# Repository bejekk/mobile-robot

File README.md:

# Robot mobilny — praca inżynierska

Konstrukcja i oprogramowanie czterokołowego (gąsienicowego) robota mobilnego.
Firmware czasu rzeczywistego na **STM32H755**, sterowanie z **ROS 2 Humble** na Jetson Nano, płyta główna w **KiCad** oraz modele mechaniczne przekładni i obudowy.

Autor: **Błażej Kruszka**, Uniwersytet Mikołaja Kopernika w Toruniu, 2025–2026.

## Architektura

```
gamepad  →  ROS 2 (Jetson)  →  UART 115200  →  STM32H755
                 │                                  │
                 └── /telemetry ← prędkości PI ← enkodery DC, PWM, A4988
```

- **STM32 (CM7)** — enkodery, regulatory PI, mostki H (4× DC), silniki krokowe (4× A4988), protokół UART.
- **ROS 2** — odczyt pada, mostek szeregowy, logger telemetrii.
- **PCB** — płyta główna pod Nucleo-H755, 8 kanałów wykonawczych i interfejsy czujników.

## Struktura repozytorium

| Katalog | Zawartość |
| --- | --- |
| `firmware/` | Projekt STM32CubeIDE (dual-core STM32H755ZITX), bez artefaktów kompilacji |
| `ros2_ws/` | Pakiet `robot_control` + Dockerfile |
| `pcb/` | KiCad (schemat, PCB, Gerber) |
| `mechanical/` | Modele STL i archiwum Fusion 360 |
| `control/` | Skrypt MATLAB do identyfikacji regulatorów PI |
| `docs/` | Praca, prezentacja, opis protokołu UART |

Nie ma tu notatek roboczych, dumpów CubeIDE, kopii zapasowych KiCad, filmów ani cudzych prac.

## Firmware (STM32)

Otwórz folder `firmware/` w STM32CubeIDE (projekt dual-core nadal nazywa się `jakie_wyjscia` — tak zapisał CubeMX). Zbuduj konfigurację **CM7 Debug** oraz CM4, jeśli boot dual-core ma zostać zachowany.

Aplikacja użytkownika:

- `firmware/CM7/Core/Src/PI.c` — pomiar prędkości z enkodera, filtr i regulator PI z rampą oraz anti-windup
- `firmware/CM7/Core/Src/motor_control.c` — PWM + kierunek mostka H, sleep/dir silników krokowych
- `firmware/CM7/Core/Src/main.c` — parser UART, pętla 10 ms, telemetria

Po resecie STM32 czeka na komendę `ready` (buzzer), dopiero potem przyjmuje zadawanie prędkości i krokowych.

## ROS 2

Wymagania: ROS 2 Humble, `python3-serial`, pakiet `inputs`.

```bash
cd ros2_ws
source /opt/ros/humble/setup.bash
colcon build --symlink-install
source install/setup.bash
ros2 launch robot_control robot.launch.py
```

Port UART można zmienić parametrem węzła `stm_bridge`:

```bash
ros2 run robot_control stm_bridge --ros-args -p port:=/dev/ttyACM0 -p baudrate:=115200
```

### Docker (Jetson)

```bash
cd ros2_ws
sudo docker build -t robot_control:humble .
xhost +local:root
sudo docker run -it --rm --network host \
  --runtime nvidia \
  -e DISPLAY=$DISPLAY \
  -v /tmp/.X11-unix:/tmp/.X11-unix \
  --device /dev/input/js0 \
  --device /dev/ttyACM0 \
  robot_control:humble
```

W kontenerze: `source /home/ros_user/ws/install/setup.bash && ros2 launch robot_control robot.launch.py`.

## MATLAB

`control/pi_identification.m` wysyła sekwencję skoków `lspeed`/`rspeed` i rysuje zadanie vs. pomiar dla czterech kół. Ustaw `portName` na swój port (`COM18` w Windows, `/dev/ttyACM0` w Linux).

## PCB

Projekt KiCad 8: `pcb/PCBV2.kicad_pro`. Gerbery do produkcji są w `pcb/gerber/`. Podgląd schematu: `pcb/PCBV2.pdf`.

## Protokół UART

Zobacz [docs/uart.md](docs/uart.md).

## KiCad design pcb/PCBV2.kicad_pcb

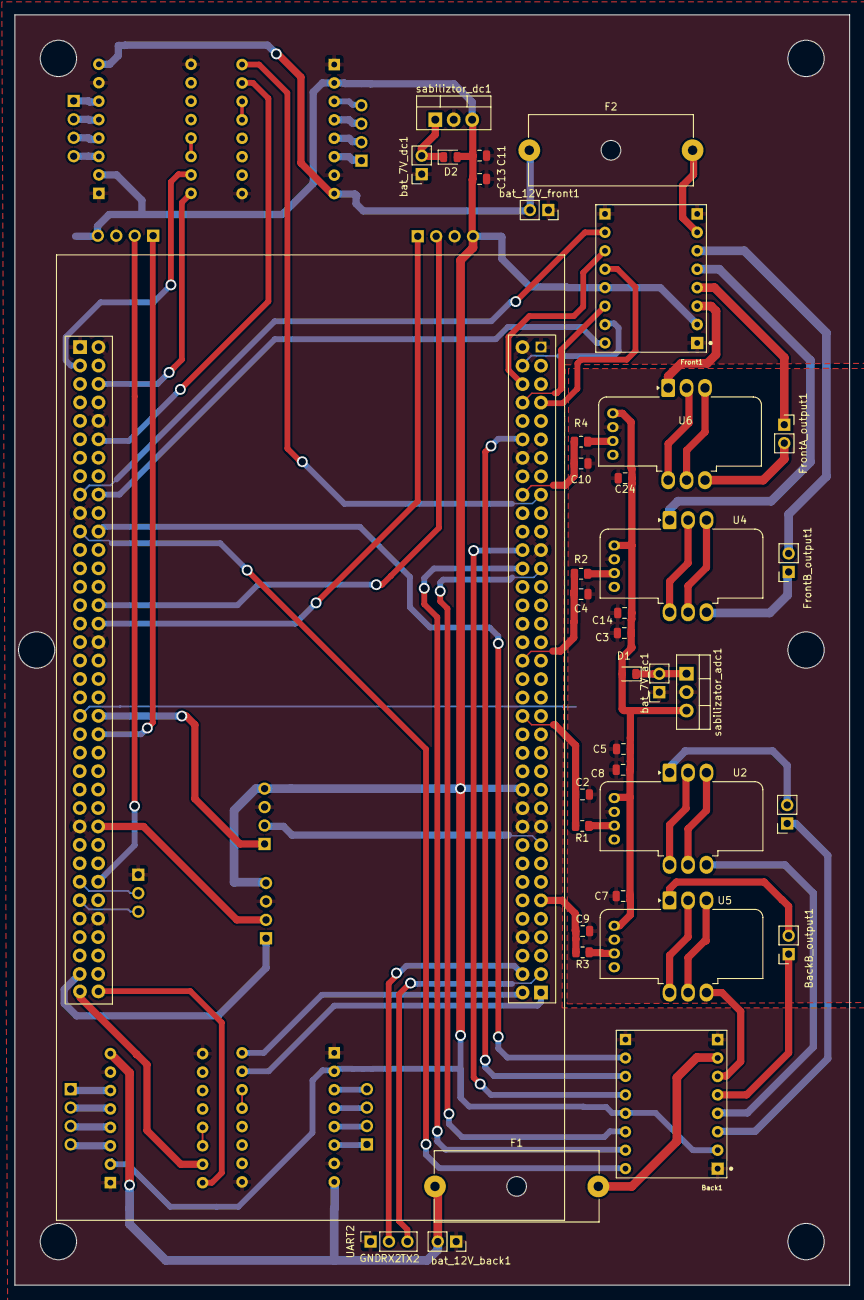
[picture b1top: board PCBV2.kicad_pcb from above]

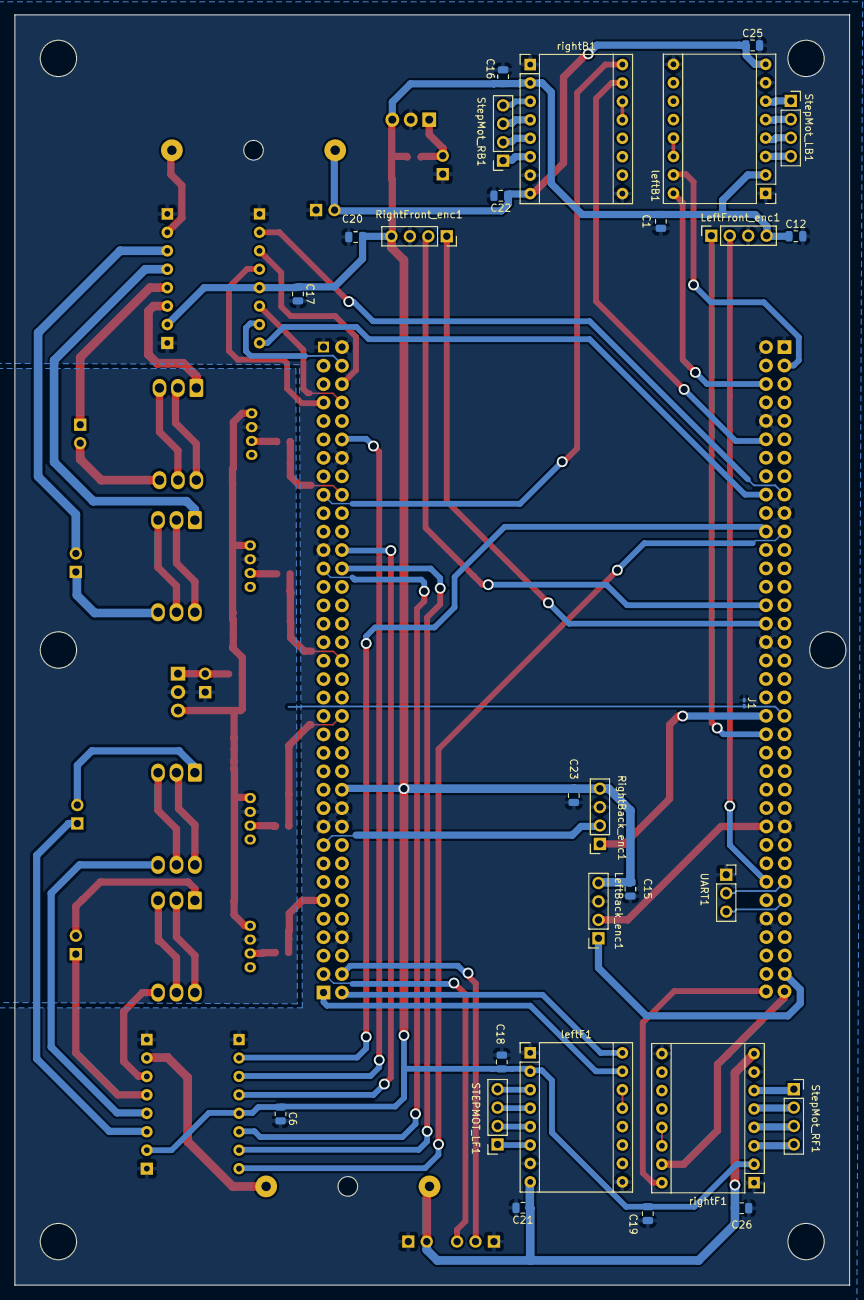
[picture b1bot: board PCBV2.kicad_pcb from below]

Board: 4 copper layers, 115.0 x 175.0 mm, 66 parts (28 on the bottom side), 89 nets.

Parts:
Back1: TB6612FNG; SHIELD_POLOLU-713
BackB_output1: PinSocket_1x02_P2.54mm_Vertical
BazkB_output1: PinSocket_1x02_P2.54mm_Vertical
C1, C2, C3, C4, C6, C7, C8, C9, C10, C11, C12, C14, C15, C16, C17, C18, C19, C20, C21, C22, C23, C24, C25, C26: 100nF; C_0805_2012Metric
C5, C13: 100uF; C_0805_2012Metric
D1, D2: D_Filled; D_0805_2012Metric
F1, F2: Fuse; Fuseholder_Cylinder-5x20mm_Schurter_0031_8201_Horizontal_Op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
Front1: TB6612FNG; SHIELD_POLOLU-713
FrontA_output1: PinSocket_1x02_P2.54mm_Vertical
FrontB_output1: PinSocket_1x02_P2.54mm_Vertical
J1: zworaGND; R_0201_0603Metric_Pad0.64x0.40mm_HandSolder
LeftBack_enc1: Conn_01x04_Pin; PinSocket_1x04_P2.54mm_Vertical
LeftFront_enc1: Conn_01x04_Pin; PinSocket_1x04_P2.54mm_Vertical
R1, R2, R3, R4: 3.2K; R_0805_2012Metric
RightBack_enc1: Conn_01x04_Pin; PinSocket_1x04_P2.54mm_Vertical
RightFront_enc1: Conn_01x04_Pin; PinSocket_1x04_P2.54mm_Vertical
STEPMOT_LF1: Conn_01x04_Pin; PinSocket_1x04_P2.54mm_Vertical
StepMot_LB1: Conn_01x04_Pin; PinSocket_1x04_P2.54mm_Vertical
StepMot_RB1: Conn_01x04_Pin; PinSocket_1x04_P2.54mm_Vertical
StepMot_RF1: Conn_01x04_Pin; PinSocket_1x04_P2.54mm_Vertical
U1: STM32H755
U2, U4, U5, U6: LTSR6-NP; LEM_LTSR-NP
UART1: UART1; PinSocket_1x03_P2.54mm_Vertical
UART2: UART2; PinSocket_1x03_P2.54mm_Vertical
bat_7V_ac1, bat_7V_dc1, bat_12V_back1, bat_12V_front1: PinSocket_1x02_P2.54mm_Vertical
leftB1: Pololu_Breakout_A4988; Pololu_Breakout-16_15.2x20.3mm
leftF1: Pololu_Breakout_A4988; Pololu_Breakout-16_15.2x20.3mm
rightB1: Pololu_Breakout_A4988; Pololu_Breakout-16_15.2x20.3mm
rightF1: Pololu_Breakout_A4988; Pololu_Breakout-16_15.2x20.3mm
sabilizator_adc1: LM2940T-5.0_NOPB; TO-220-3_Vertical
sabiliztor_dc1: LM2940T-5.0_NOPB; TO-220-3_Vertical

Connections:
7V: D1.1 (K), D2.1 (K), bat_7V_ac1.2, bat_7V_dc1.2, sabilizator_adc1.1 (IN), sabiliztor_dc1.1 (IN)
12V: C21.1, C22.1, C25.1, C26.1, F1.1, F2.1, bat_12V_back1.2, bat_12V_front1.2, leftB1.8 (VMOT), leftF1.8 (VMOT), rightB1.8 (VMOT), rightF1.8 (VMOT)
+5V: Back1.2 (VCC), Back1.13 (STBY), C1.1, C6.1, C11.2, C12.1, C13.1, C15.1, C16.1, C17.1, C18.1, C19.1, C20.1, C23.1, D2.2 (A), Front1.2 (VCC), Front1.13 (STBY), LeftBack_enc1.4, LeftFront_enc1.4, RightBack_enc1.4, RightFront_enc1.4, U1.VIN, leftB1.2 (VDD), leftF1.2 (VDD), rightB1.2 (VDD), rightF1.2 (VDD), sabiliztor_dc1.3 (OUT)
+5VA: C3.2, C5.1, C7.1, C8.1, C14.1, C24.1, D1.2 (A), U2.10 (+5V), U4.10 (+5V), U5.10 (+5V), U6.10 (+5V), sabilizator_adc1.3 (OUT)
/ADC1: C2.1, R1.2, U1.PA4
/ADC2: C4.2, R2.2, U1.PC0
/ADC3: C9.1, R3.2, U1.PF7
/ADC4: C10.2, R4.2, U1.PF9
/AIN1_Back: Back1.14 (AIN1), U1.PE3
/AIN1_Front: Front1.14 (AIN1), U1.PG10
/AIN2_Back: Back1.15 (AIN2), U1.PE4
/AIN2_Front: Front1.15 (AIN2), U1.PG11
/BIN1_Back: Back1.12 (BIN1), U1.PE5
/BIN1_Front: Front1.12 (BIN1), U1.PG12
/BIN2_Back: Back1.11 (BIN2), U1.PE6
/BIN2_Front: Front1.11 (BIN2), U1.PG13
/DIR_LB: U1.PG7, leftB1.16 (DIR)
/DIR_LF: U1.PC11, leftF1.16 (DIR)
/DIR_RB: U1.PD1, rightB1.16 (DIR)
/DIR_RF: U1.PC9, rightF1.16 (DIR)
/LB_encA: LeftBack_enc1.1, U1.PC6
/LB_encB: LeftBack_enc1.2, U1.PC7
/LF_encA: LeftFront_enc1.2, U1.PA6
/LF_encB: LeftFront_enc1.1, U1.PB5
/PWMA_B: Back1.16 (PWMA), U1.PE9
/PWMA_F: Front1.16 (PWMA), U1.PE13
/PWMB_B: Back1.10 (PWMB), U1.PE14
/PWMB_F: Front1.10 (PWMB), U1.PE11
/RB_encA: RightBack_enc1.2, U1.PA15
/RB_encB: RightBack_enc1.1, U1.PB3
/RF_encA: RightFront_enc1.2, U1.PD12
/RF_encB: RightFront_enc1.1, U1.PD13
/RX1: U1.PA11, UART1.2
/RX2: U1.PD2, UART2.2
/STEP_LB: U1.PG6, leftB1.15 (STEP)
/STEP_LF: U1.PC10, leftF1.15 (STEP)
/STEP_RB: U1.PG14, rightB1.15 (STEP)
/STEP_RF: U1.PC8, rightF1.15 (STEP)
/SensBAIN: Back1.4 (AO2), U2.4 (OUT4)
/SensBAOut: BazkB_output1.2, U2.1 (IN1)
/SensBBIN: Back1.6 (BO1), U5.4 (OUT4)
/SensBBOut: BackB_output1.2, U5.1 (IN1)
/SensFAIN: Front1.3 (AO1), U6.1 (IN1)
/SensFAOut: FrontA_output1.2, U6.4 (OUT4)
/SensFBIN: Front1.5 (BO2), U4.1 (IN1)
/SensFBOut: FrontB_output1.1, U4.4 (OUT4)
/TX1: U1.PA12, UART1.3
/TX2: U1.PC12, UART2.3
GND: Back1.1 (GND), Back1.8 (PGND1), Back1.9 (PGND2), C1.2, C6.2, C11.1, C12.2, C13.2, C15.2, C16.2, C17.2, C18.2, C19.2, C20.2, C21.2, C22.2, C23.2, C25.2, C26.2, Front1.1 (GND), Front1.8 (PGND1), Front1.9 (PGND2), J1.1, LeftBack_enc1.3, LeftFront_enc1.3, RightBack_enc1.3, RightFront_enc1.3, U1.GND, UART1.1, UART2.1, bat_7V_dc1.1, bat_12V_back1.1, bat_12V_front1.1, leftB1.1 (GND), leftB1.7 (GND), leftB1.9 (~ENABLE), leftF1.1 (GND), leftF1.7 (GND), leftF1.9 (~ENABLE), rightB1.1 (GND), rightB1.7 (GND), rightB1.9 (~ENABLE), rightF1.1 (GND), rightF1.7 (GND), rightF1.9 (~ENABLE), sabiliztor_dc1.2 (GND)
GNDA: C2.2, C3.1, C4.1, C5.2, C7.2, C8.2, C9.2, C10.1, C14.2, C24.2, U2.9 (0V), U4.9 (0V), U5.9 (0V), U6.9 (0V), bat_7V_ac1.1, sabilizator_adc1.2 (GND)
unnamed: Back1.3 (AO1), BazkB_output1.1
unnamed: Back1.5 (BO2), BackB_output1.1
unnamed: Back1.7 (VMOT), F1.2
unnamed: Front1.4 (AO2), FrontA_output1.1
unnamed: Front1.6 (BO1), FrontB_output1.2
unnamed: F2.2, Front1.7 (VMOT)
unnamed: J1.2, U1.AGND
unnamed: STEPMOT_LF1.1, leftF1.6 (2B)
unnamed: STEPMOT_LF1.2, leftF1.5 (2A)
unnamed: STEPMOT_LF1.3, leftF1.4 (1A)
unnamed: STEPMOT_LF1.4, leftF1.3 (1B)
unnamed: StepMot_LB1.1, leftB1.6 (2B)
unnamed: StepMot_LB1.2, leftB1.5 (2A)
unnamed: StepMot_LB1.3, leftB1.4 (1A)
unnamed: StepMot_LB1.4, leftB1.3 (1B)
unnamed: StepMot_RB1.1, rightB1.6 (2B)
unnamed: StepMot_RB1.2, rightB1.5 (2A)
unnamed: StepMot_RB1.3, rightB1.4 (1A)
unnamed: StepMot_RB1.4, rightB1.3 (1B)
unnamed: StepMot_RF1.1, rightF1.6 (2B)
unnamed: StepMot_RF1.2, rightF1.5 (2A)
unnamed: StepMot_RF1.3, rightF1.4 (1A)
unnamed: StepMot_RF1.4, rightF1.3 (1B)
unnamed: U2.2 (IN2), U2.6 (OUT6)
unnamed: U2.3 (IN3), U2.5 (OUT5)
unnamed: R1.1, U2.8 (Out)
unnamed: U4.2 (IN2), U4.6 (OUT6)
unnamed: U4.3 (IN3), U4.5 (OUT5)
unnamed: R2.1, U4.8 (Out)
unnamed: U5.2 (IN2), U5.6 (OUT6)
unnamed: U5.3 (IN3), U5.5 (OUT5)
unnamed: R3.1, U5.8 (Out)
unnamed: U6.2 (IN2), U6.6 (OUT6)
unnamed: U6.3 (IN3), U6.5 (OUT5)
unnamed: R4.1, U6.8 (Out)
unnamed: leftB1.13 (~RESET), leftB1.14 (~SLEEP)
unnamed: leftF1.13 (~RESET), leftF1.14 (~SLEEP)
unnamed: rightB1.13 (~RESET), rightB1.14 (~SLEEP)
unnamed: rightF1.13 (~RESET), rightF1.14 (~SLEEP)

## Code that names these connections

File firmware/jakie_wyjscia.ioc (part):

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Mcu.Name=STM32H755ZITx
Mcu.Package=LQFP144
Mcu.UserName=STM32H755ZITx
PA0.GPIOParameters=PinAttribute
PA0.Mode=MII
PA0.PinAttribute=CortexM7
PA0.Signal=ETH_CRS
PA1.GPIOParameters=PinAttribute
PA1.Mode=MII
PA1.PinAttribute=CortexM7
PA1.Signal=ETH_RX_CLK
PA11.GPIOParameters=PinAttribute
PA11.Mode=Asynchronous
PA11.PinAttribute=CortexM7
PA11.Signal=UART4_RX
PA12.GPIOParameters=PinAttribute
PA12.Mode=Asynchronous
PA12.PinAttribute=CortexM7
PA12.Signal=UART4_TX
PA15\ (JTDI).GPIOParameters=PinAttribute
PA15\ (JTDI).PinAttribute=CortexM7
PA15\ (JTDI).Signal=S_TIM2_CH1_ETR
PA2.GPIOParameters=PinAttribute
PA2.Mode=MII
PA2.PinAttribute=CortexM7
PA2.Signal=ETH_MDIO
PA3.GPIOParameters=PinAttribute
PA3.Mode=MII
PA3.PinAttribute=CortexM7
PA3.Signal=ETH_COL
PA5.GPIOParameters=PinAttribute
PA5.Mode=Full_Duplex_Master
PA5.PinAttribute=CortexM7
PA5.Signal=SPI1_SCK
PA6.GPIOParameters=PinAttribute
PA6.PinAttribute=CortexM7
PA6.Signal=S_TIM3_CH1
PA7.GPIOParameters=PinAttribute
PA7.Mode=MII
PA7.PinAttribute=CortexM7
PA7.Signal=ETH_RX_DV
PB0.GPIOParameters=PinAttribute
PB0.Mode=MII
PB0.PinAttribute=CortexM7
PB0.Signal=ETH_RXD2
PB1.GPIOParameters=PinAttribute
PB1.Mode=MII
PB1.PinAttribute=CortexM7
PB1.Signal=ETH_RXD3
PB11.GPIOParameters=PinAttribute
PB11.Mode=MII
PB11.PinAttribute=CortexM7
PB11.Signal=ETH_TX_EN
PB12.GPIOParameters=PinAttribute
PB12.Mode=MII
PB12.PinAttribute=CortexM7
PB12.Signal=ETH_TXD0
PB13.GPIOParameters=PinAttribute
PB13.Mode=MII
PB13.PinAttribute=CortexM7
PB13.Signal=ETH_TXD1
PB3\ (JTDO/TRACESWO).GPIOParameters=PinAttribute
PB3\ (JTDO/TRACESWO).PinAttribute=CortexM7
PB3\ (JTDO/TRACESWO).Signal=S_TIM2_CH2
PB5.GPIOParameters=PinAttribute
PB5.PinAttribute=CortexM7
PB5.Signal=S_TIM3_CH2
PB6.GPIOParameters=PinAttribute
PB6.Mode=I2C
PB6.PinAttribute=CortexM7
PB6.Signal=I2C1_SCL
PB7.GPIOParameters=PinAttribute
PB7.Mode=I2C
PB7.PinAttribute=CortexM7
PB7.Signal=I2C1_SDA
PB8.ContextOwner=CortexM7
PB8.GPIOParameters=GPIO_Label,GPIO_FM8,PinAttribute
PB8.GPIO_FM8=__NULL
PB8.GPIO_Label=SLEEP_RF
PB8.PinAttribute=CortexM7
PB8.Signal=GPIO_Output
PB9.ContextOwner=CortexM7
PB9.GPIOParameters=GPIO_Label,PinAttribute,GPIO_FM9
PB9.GPIO_FM9=__NULL
PB9.GPIO_Label=SLEEP_LF
PB9.PinAttribute=CortexM7
PB9.Signal=GPIO_Output
PC0.GPIOParameters=PinAttribute
PC0.PinAttribute=CortexM7
PC0.Signal=ADCx_INP10
PC1.GPIOParameters=PinAttribute
PC1.Mode=MII
PC1.PinAttribute=CortexM7
PC1.Signal=ETH_MDC
PC10.ContextOwner=CortexM7
PC10.GPIOParameters=GPIO_Label,PinAttribute
PC10.GPIO_Label=STEP_LF
PC10.PinAttribute=CortexM7
PC10.Signal=GPIO_Output
PC11.ContextOwner=CortexM7
PC11.GPIOParameters=GPIO_Label,PinAttribute
PC11.GPIO_Label=DIR_LF
PC11.PinAttribute=CortexM7
PC11.Signal=GPIO_Output
PC12.GPIOParameters=PinAttribute
PC12.Mode=Asynchronous
PC12.PinAttribute=CortexM7
PC12.Signal=UART5_TX
PC2_C.GPIOParameters=PinAttribute
PC2_C.Mode=MII
PC2_C.PinAttribute=CortexM7
PC2_C.Signal=ETH_TXD2
PC3_C.GPIOParameters=PinAttribute
PC3_C.Mode=MII
PC3_C.PinAttribute=CortexM7
PC3_C.Signal=ETH_TX_CLK
PC4.GPIOParameters=PinAttribute
PC4.Mode=MII
PC4.PinAttribute=CortexM7
PC4.Signal=ETH_RXD0
PC5.GPIOParameters=PinAttribute
PC5.Mode=MII
PC5.PinAttribute=CortexM7
PC5.Signal=ETH_RXD1
PC6.GPIOParameters=PinAttribute
PC6.PinAttribute=CortexM7
PC6.Signal=S_TIM8_CH1
PC7.GPIOParameters=PinAttribute
PC7.PinAttribute=CortexM7
PC7.Signal=S_TIM8_CH2
PC8.ContextOwner=CortexM7
PC8.GPIOParameters=GPIO_Label,PinAttribute
PC8.GPIO_Label=STEP_RF
PC8.PinAttribute=CortexM7
PC8.Signal=GPIO_Output
PC9.ContextOwner=CortexM7
PC9.GPIOParameters=GPIO_Label,PinAttribute
PC9.GPIO_Label=DIR_RF
PC9.PinAttribute=CortexM7
PC9.Signal=GPIO_Output
PD1.ContextOwner=CortexM7
PD1.GPIOParameters=GPIO_Label,PinAttribute
PD1.GPIO_Label=DIR_RB
PD1.PinAttribute=CortexM7
PD1.Signal=GPIO_Output
PD10.ContextOwner=CortexM7
PD10.GPIOParameters=GPIO_Label,PinAttribute
PD10.GPIO_Label=SLEEP_RB
PD10.PinAttribute=CortexM7
PD10.Signal=GPIO_Output
PD12.GPIOParameters=PinAttribute
PD12.PinAttribute=CortexM7
PD12.Signal=S_TIM4_CH1
PD13.GPIOParameters=PinAttribute
PD13.PinAttribute=CortexM7
PD13.Signal=S_TIM4_CH2
PD2.GPIOParameters=PinAttribute
PD2.Mode=Asynchronous
PD2.PinAttribute=CortexM7
PD2.Signal=UART5_RX
PD6.ContextOwner=CortexM7
PD6.GPIOParameters=PinAttribute
PD6.PinAttribute=CortexM7
PD6.Signal=GPIO_Output
PD7.GPIOParameters=PinAttribute
PD7.Mode=Full_Duplex_Master
PD7.PinAttribute=CortexM7
PD7.Signal=SPI1_MOSI
PD8.GPIOParameters=PinAttribute
PD8.Mode=Asynchronous
PD8.PinAttribute=CortexM7
PD8.Signal=USART3_TX
PD9.GPIOParameters=PinAttribute
PD9.Mode=Asynchronous
PD9.PinAttribute=CortexM7
PD9.Signal=USART3_RX
PE11.GPIOParameters=PinAttribute
PE11.PinAttribute=CortexM7
PE11.Signal=S_TIM1_CH2
PE13.GPIOParameters=PinAttribute
PE13.PinAttribute=CortexM7
PE13.Signal=S_TIM1_CH3
PE14.GPIOParameters=PinAttribute
PE14.PinAttribute=CortexM7
PE14.Signal=S_TIM1_CH4
PE2.GPIOParameters=PinAttribute
PE2.Mode=MII
PE2.PinAttribute=CortexM7
PE2.Signal=ETH_TXD3
PE3.ContextOwner=CortexM7
PE3.GPIOParameters=GPIO_Label,PinAttribute
PE3.GPIO_Label=BIN1_B
PE3.PinAttribute=CortexM7
PE3.Signal=GPIO_Output
PE4.ContextOwner=CortexM7
PE4.GPIOParameters=GPIO_Label,PinAttribute
PE4.GPIO_Label=BIN2_B
PE4.PinAttribute=CortexM7
PE4.Signal=GPIO_Output
PE5.ContextOwner=CortexM7
PE5.GPIOParameters=GPIO_Label,PinAttribute
PE5.GPIO_Label=AIN1_B
PE5.PinAttribute=CortexM7
PE5.Signal=GPIO_Output
PE6.ContextOwner=CortexM7
PE6.GPIOParameters=GPIO_Label,PinAttribute
PE6.GPIO_Label=AIN2_B
PE6.PinAttribute=CortexM7
PE6.Signal=GPIO_Output
PE7.GPIOParameters=PinAttribute
PE7.Mode=Asynchronous
PE7.PinAttribute=CortexM7
PE7.Signal=UART7_RX
PE8.GPIOParameters=PinAttribute
PE8.Mode=Asynchronous
PE8.PinAttribute=CortexM7
PE8.Signal=UART7_TX
PE9.GPIOParameters=PinAttribute
PE9.PinAttribute=CortexM7
PE9.Signal=S_TIM1_CH1
PF7.GPIOParameters=PinAttribute
PF7.Mode=IN3-Single-Ended
PF7.PinAttribute=CortexM7
PF7.Signal=ADC3_INP3
PF9.GPIOParameters=PinAttribute
PF9.Mode=IN2-Single-Ended
PF9.PinAttribute=CortexM7
PF9.Signal=ADC3_INP2
PG10.ContextOwner=CortexM7
PG10.GPIOParameters=GPIO_Label,PinAttribute
PG10.GPIO_Label=BIN1_F
PG10.PinAttribute=CortexM7
PG10.Signal=GPIO_Output
PG11.ContextOwner=CortexM7
PG11.GPIOParameters=GPIO_Label,PinAttribute
PG11.GPIO_Label=BIN2_F
PG11.PinAttribute=CortexM7
PG11.Signal=GPIO_Output
PG12.ContextOwner=CortexM7
PG12.GPIOParameters=GPIO_Label,PinAttribute
PG12.GPIO_Label=AIN1_F
PG12.PinAttribute=CortexM7
PG12.Signal=GPIO_Output
PG13.ContextOwner=CortexM7
PG13.GPIOParameters=GPIO_Label,PinAttribute
PG13.GPIO_Label=AIN2_F
PG13.PinAttribute=CortexM7
PG13.Signal=GPIO_Output
PG14.ContextOwner=CortexM7
PG14.GPIOParameters=GPIO_Label,PinAttribute
PG14.GPIO_Label=STEP_RB
PG14.PinAttribute=CortexM7
PG14.Signal=GPIO_Output
PG6.ContextOwner=CortexM7
PG6.GPIOParameters=GPIO_Label,PinAttribute
PG6.GPIO_Label=STEP_LB
PG6.PinAttribute=CortexM7
PG6.Signal=GPIO_Output
PG7.ContextOwner=CortexM7
PG7.GPIOParameters=GPIO_Label,PinAttribute
PG7.GPIO_Label=DIR_LB
PG7.PinAttribute=CortexM7
PG7.Signal=GPIO_Output
PG8.ContextOwner=CortexM7
PG8.GPIOParameters=GPIO_Label,PinAttribute
PG8.GPIO_Label=SLEEP_LB
PG8.PinAttribute=CortexM7
PG8.Signal=GPIO_Output
PG9.GPIOParameters=PinAttribute
PG9.Mode=Full_Duplex_Master
PG9.PinAttribute=CortexM7
PG9.Signal=SPI1_MISO
RCC.SYSCLKFreq_VALUE=128000000
RCC.SYSCLKSource=RCC_SYSCLKSOURCE_PLLCLK
board=custom
